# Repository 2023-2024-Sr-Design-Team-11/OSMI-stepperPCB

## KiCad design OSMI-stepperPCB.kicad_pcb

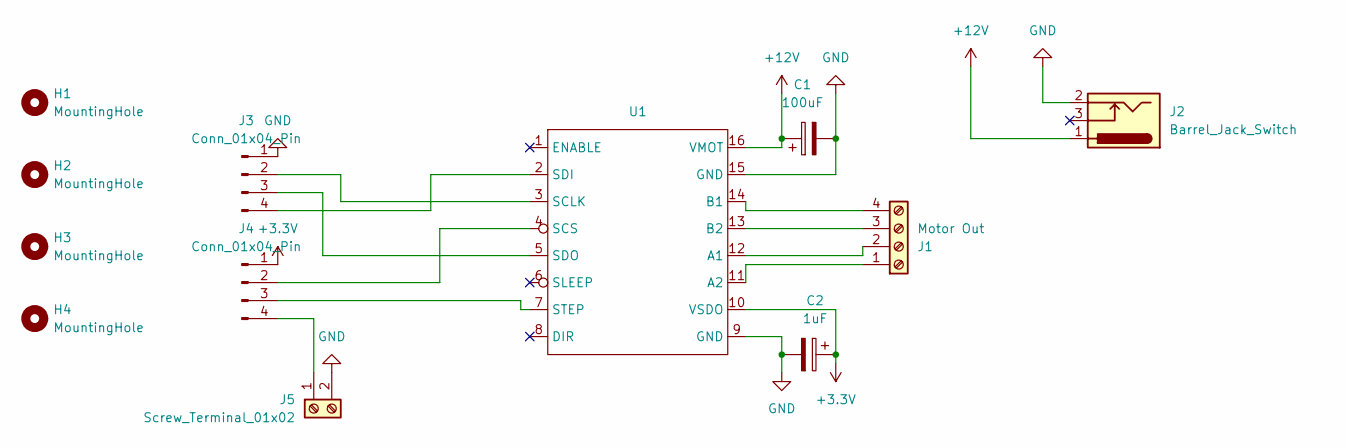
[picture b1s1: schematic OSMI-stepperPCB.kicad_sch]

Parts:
C1: 100uF; CP_Radial_D8.0mm_P2.50mm
C2: 1uF; CP_Radial_D5.0mm_P2.50mm
H1, H2, H3, H4: MountingHole; MountingHole_2.2mm_M2
J1: Motor Out; TerminalBlock_Phoenix_MPT-0,5-4-2.54_1x04_P2.54mm_Horizontal
J2: Barrel_Jack_Switch; BarrelJack_Horizontal
J3, J4: Conn_01x04_Pin; PinHeader_1x04_P2.54mm_Vertical
J5: Screw_Terminal_01x02; TerminalBlock_Phoenix_MPT-0,5-2-2.54_1x02_P2.54mm_Horizontal
U1: DIP-16_500_ELL

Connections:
+3.3V: C2.1, J4.1, U1.10 (VSDO)
+12V: C1.1, J2.1, U1.16 (VMOT)
GND: C1.2, C2.2, J2.2, J3.1, J5.2, U1.9 (GND), U1.15 (GND)
unnamed: J1.1, U1.11 (A2)
unnamed: J1.2, U1.12 (A1)
unnamed: J1.3, U1.13 (B2)
unnamed: J1.4, U1.14 (B1)
unnamed: J3.2, U1.3 (SCLK)
unnamed: J3.3, U1.5 (SDO)
unnamed: J3.4, U1.2 (SDI)
unnamed: J4.2, U1.4 (SCS)
unnamed: J4.3, U1.7 (STEP)
unnamed: J4.4, J5.1

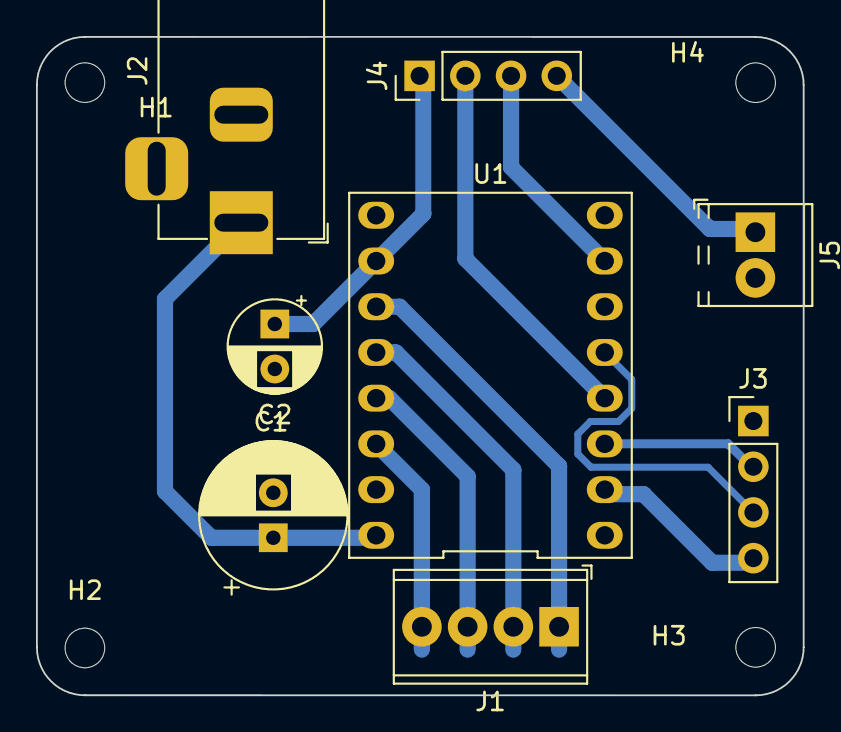
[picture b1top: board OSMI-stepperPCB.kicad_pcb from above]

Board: 2 copper layers, 42.6 x 36.6 mm, 12 parts (0 on the bottom side), 13 nets.

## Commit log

2024-02-18 First revision
